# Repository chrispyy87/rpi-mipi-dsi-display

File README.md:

# rpi-mipi-dsi-display
Raspberry CM4 MIPI DSI display shield with LED driver for Midas MDT0500B1IH-MIPI display https://midasdisplays.com/shop/tft/mdt0500b1ih-mipi/ employing the ILI9881C display driver.
This shield serves as a example on how to implement alternative MIPI DSI displays to currently support ones.
PCBA manufacturing was realized by JLCPCB.

## Contents
- KiCAD schematics/board files: [CAD](CAD/)
- Gerber files: [rpi-mipi-dsi-display.zip](CAD/production/rpi-mipi-dsi-display.zip)
- PDF of schematics: [rpi-mipi-dsi-display.pdf](CAD/rpi-mipi-dsi-display.pdf)
- Bill of Materials: [rpi-mipi-dsi-display-BOM.xlsx](CAD/assembly/rpi-mipi-dsi-display-BOM.xlsx)
- KiCAD PCB and pick & place files: [rpi-mipi-dsi-display_CPL1.xlsx](CAD/assembly/rpi-mipi-dsi-display_CPL1.xlsx)

## Status
Working prototype with CM4 IO board running RPI OS Bookworm (64 bit).

## Copyright and License
Schematic and PCB layout files are licensed under the CC BY 4.0 license.

THE DESIGN IS PROVIDED "AS IS" AND THE AUTHOR DISCLAIMS ALL WARRANTIES WITH REGARD TO THIS DESIGN INCLUDING ALL IMPLIED WARRANTIES OF MERCHANTABILITY AND FITNESS. IN NO EVENT SHALL THE AUTHOR BE LIABLE FOR ANY SPECIAL, DIRECT, INDIRECT, OR CONSEQUENTIAL DAMAGES OR ANY DAMAGES WHATSOEVER RESULTING FROM LOSS OF USE, DATA OR PROFITS, WHETHER IN AN ACTION OF CONTRACT, NEGLIGENCE OR OTHER TORTIOUS ACTION, ARISING OUT OF OR IN CONNECTION WITH THE USE OR PERFORMANCE OF THIS DESIGN.

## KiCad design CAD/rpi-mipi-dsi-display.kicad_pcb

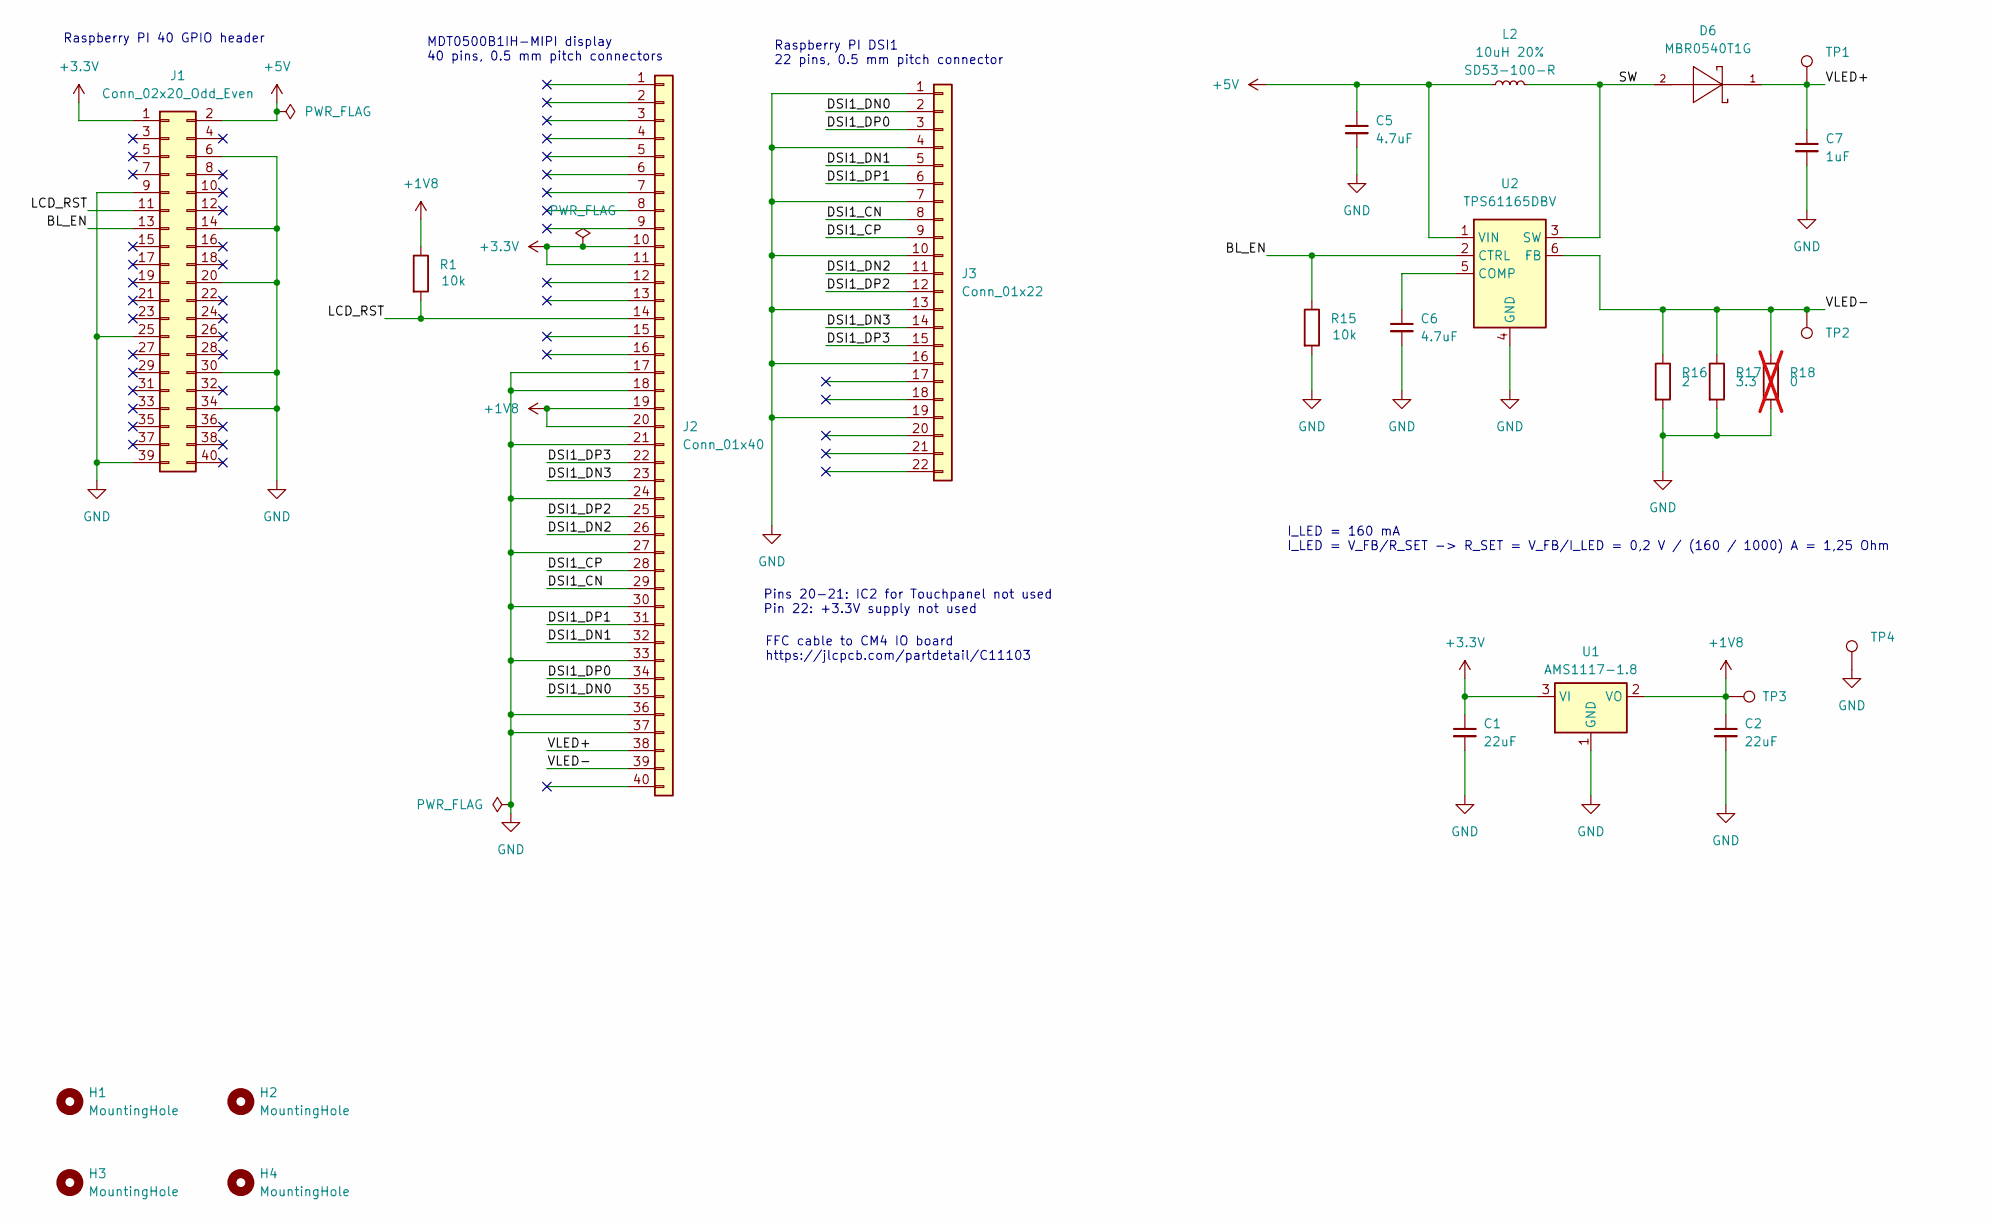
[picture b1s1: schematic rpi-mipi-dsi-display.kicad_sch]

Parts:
C1, C2: 22uF; C_0603_1608Metric
C5, C6: 4.7uF; C_0603_1608Metric
C7: 1uF; C_0603_1608Metric
D6: MBR0540T1G; SOD-123; MANUFACTURER_PART_NUMBER MBR0540T1G
H1, H2, H3, H4: MountingHole; MountingHole_3.5mm_Pad
J1: Conn_02x20_Odd_Even; PinSocket_2x20_P2.54mm_Vertical
J2: Conn_01x40; Hirose_FH12-40S-0.5SH_1x40-1MP_P0.50mm_Horizontal_PiPad
J3: Conn_01x22; Hirose_FH12-22S-0.5SH_1x22-1MP_P0.50mm_Horizontal_PiPad
L2: 10uH 20%; SD53-100-R
R1, R15: 10k; R_0603_1608Metric_Pad0.98x0.95mm_HandSolder; MPN RC0603FR-072K2L; Digi-Key_PN 311-2.20KHRCT-ND
R16: 2; R_0603_1608Metric_Pad0.98x0.95mm_HandSolder; MPN RC0603FR-072K2L; Digi-Key_PN 311-2.20KHRCT-ND
R17: 3.3; R_0603_1608Metric_Pad0.98x0.95mm_HandSolder; MPN RC0603FR-072K2L; Digi-Key_PN 311-2.20KHRCT-ND
R18: 0; R_0603_1608Metric_Pad0.98x0.95mm_HandSolder; MPN RC0603FR-072K2L; Digi-Key_PN 311-2.20KHRCT-ND; not fitted
TP1, TP2, TP3, TP4: TestPoint; TestPoint_Pad_D1.0mm
U1: AMS1117-1.8; SOT-223-3_TabPin2
U2: TPS61165DBV; SOT-23-6

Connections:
+1V8: C2.1, J2.19, J2.20, R1.1, TP3.1, U1.2 (VO)
+3.3V: C1.1, J1.1, J2.10, J2.11, U1.3 (VI)
+5V: C5.1, J1.2, L2.1, U2.1 (VIN)
/BL_EN: J1.13, R15.1, U2.2 (CTRL)
/DSI1_CN: J2.29, J3.8
/DSI1_CP: J2.28, J3.9
/DSI1_DN0: J2.35, J3.2
/DSI1_DN1: J2.32, J3.5
/DSI1_DN2: J2.26, J3.11
/DSI1_DN3: J2.23, J3.14
/DSI1_DP0: J2.34, J3.3
/DSI1_DP1: J2.31, J3.6
/DSI1_DP2: J2.25, J3.12
/DSI1_DP3: J2.22, J3.15
/LCD_RST: J1.11, J2.14, R1.2
/SW: D6.2, L2.2, U2.3 (SW)
/VLED+: C7.1, D6.1, J2.38, TP1.1
/VLED-: J2.39, R16.1, R17.1, R18.1, TP2.1, U2.6 (FB)
GND: C1.2, C2.2, C5.2, C6.2, C7.2, J1.6, J1.9, J1.14, J1.20, J1.25, J1.30, J1.34, J1.39, J2.17, J2.18, J2.21, J2.24, J2.27, J2.30, J2.33, J2.36, J2.37, J3.1, J3.4, J3.7, J3.10, J3.13, J3.16, J3.19, R15.2, R16.2, R17.2, R18.2, TP4.1, U1.1 (GND), U2.4 (GND)
unnamed: C6.1, U2.5 (COMP)

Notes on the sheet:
MDT0500B1IH-MIPI display 40 pins, 0.5 mm pitch connectors
Raspberry PI DSI1 22 pins, 0.5 mm pitch connector
I_LED = 160 mA I_LED = V_FB/R_SET -> R_SET = V_FB/I_LED = 0,2 V / (160 / 1000) A = 1,25 Ohm
FFC cable to CM4 IO board https://jlcpcb.com/partdetail/C11103
Raspberry PI 40 GPIO header
Pins 20-21: IC2 for Touchpanel not used Pin 22: +3.3V supply not used

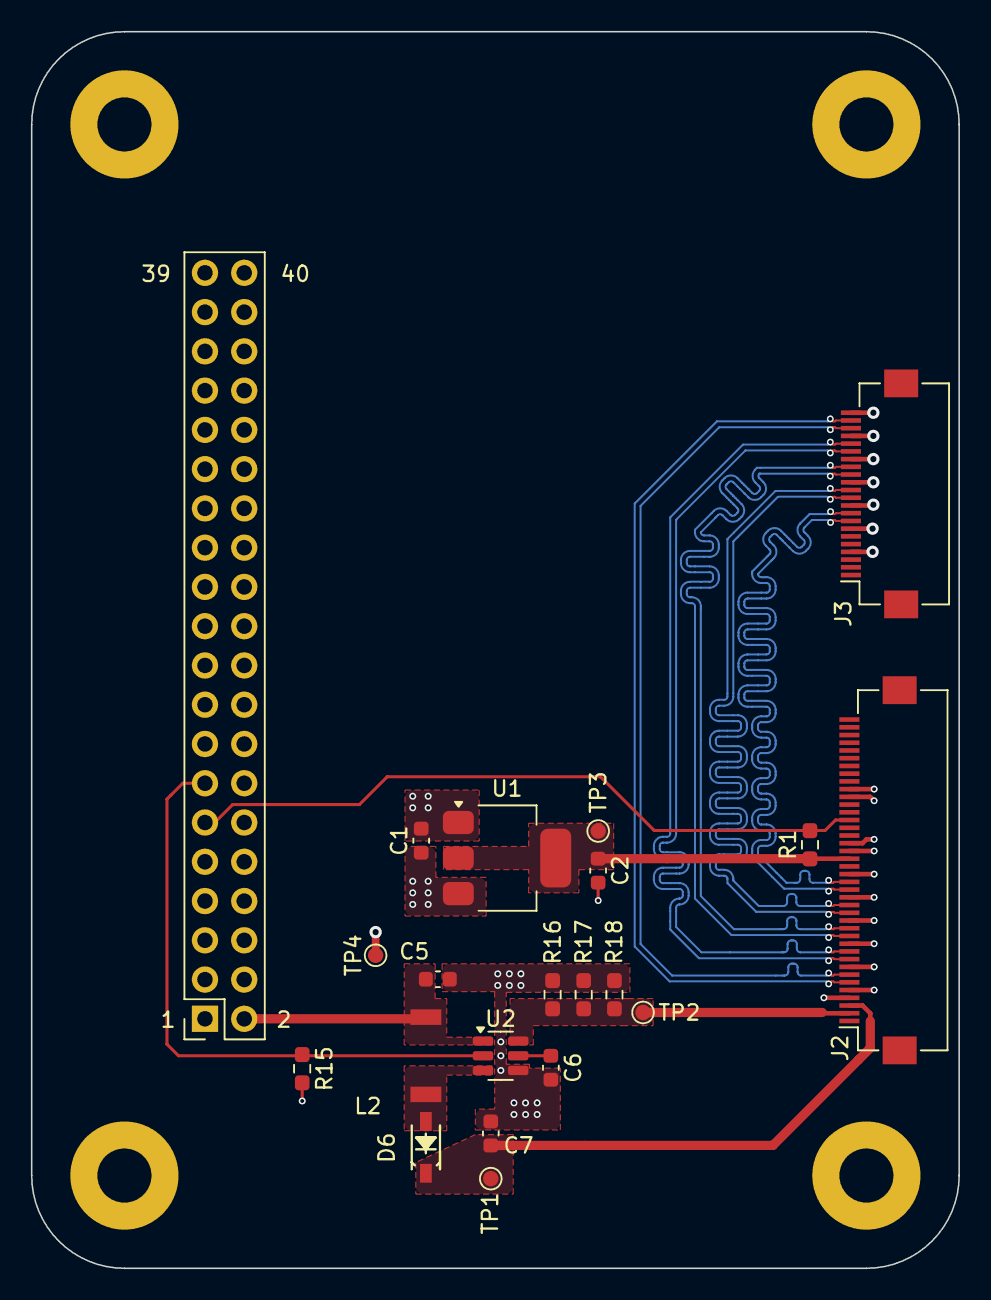
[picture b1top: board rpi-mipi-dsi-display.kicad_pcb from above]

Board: 4 copper layers, 60.0 x 80.0 mm, 25 parts (0 on the bottom side), 20 nets.

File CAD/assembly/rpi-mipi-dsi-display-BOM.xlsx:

Comment | Designator | Footprint | JLCPCB Part #（optional）
MBR0540T1G | D6 |  | C21353
AMS1117-1.8 | U1 |  | C6185
TPS61165DBV | U2 |  | C58756
Hirose_FH12-22S-0.5SH_1x22-1MP_P0.50mm_Horizontal | J3 |  | C597981
Hirose_FH12-40S-0.5SH_1x40-1MP_P0.50mm_Horizontal | J2 |  | C202114
22uF | C1, C2 | 0603 | C59461
4.7uF | C5, C6 | 0603 | C19666
1uF | C7 | 0603 | C15849
10k | R1, R15 | 0603 | C25804
2 | R16 | 0603 | C22977
3.3 | R17 | 0603 | C22979
10uH 20% | L2 |  | C7309744

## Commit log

2025-05-02 Updated readme file
2025-05-06 Updated CAD file names
2025-05-06 Added new images for docs
